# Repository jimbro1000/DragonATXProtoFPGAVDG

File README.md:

# Dragon ATX Prototype FPGA VDG

This repository contains the KiCad project files
to produce the VDG component board for my
ATX Prototype backplane.

This design requires the ATX backplane board in order 
to operate
See https://github.com/jimbro1000/DragonATXProto

## Notes

Revision 1 includes a more modern RGB fed modulator
design that removes a significant problem in the 
form of the old LM1889 modulator. The board also
provides the mounting points for the various mezzanine
boards that have been previously developed. If the
mezzanine option is to be used the rest of the card
should be left unpopulated

This design has been completed using KiCad 9. Earlier
versions of KiCad are not compatible

## Memory Map

| Address Range | Usage | Notes |
|:------------- |:----- |:----- |
| $0000 - $7FFF | Lower 32K RAM page | Can be remapped to the upper 32K using P1 under RAM/ROM memory map type |
| $8000 - $9FFF | Lower system ROM (R0) | The last 16 bytes are mapped to $FFF0 - $FFFF |
| $A000 - $BFFF | Upper system ROM (R1) | |
| $C000 - $FF00 | External ROM (R2) | |
| $C000 - $FF00 | Upper 32K RAM page | Under RAM only memory map type |
| $FF00 - $FFEF | SAM registers and Peripheral IO |
| $FF00 - $FF1F | PIA 0 & Serial port |
| $FF20 - $FF23 | PIA 1 |
| $FF24 - $FF27 | PIA 1b | video expansion slot |
| $FF28 - $FF2F | PIA 1c and 1d | audio expansion slot |
| $FF30 - $FF37 | PIA 1e and 1f | expansion slot 3 |
| $FF38 - $FF3F | PIA 1g and 1h | expansion slot 4 |
| $FF40 - $FF5F | PIA 2 | external |
| $FF60 - $FFBF | reserved |
| $FF90 | Set compatible mode | bit 7 (1) |
| $FF91 | Set task id | bits 0..2 (2)(3) |
| $FF92 | IRQ control bits | (4) |
| $FF93 | FIRQ control bits | (4) |
| $FF94 | MSB of timer |
| $FF95 | LSB of timer |
| $FFA0 | Select RAM paging register | Registers are selected for the current task only |
| $FFA1 | Upper byte of page register | |
| $FFA2 | Lower byte of page register | Writing to the lower byte commits changes to the selected register |
| $FFC0 - $FFDF | SAM |
| $FFE0 - $FFEF | reserved |
| $FFF0 - $FFFF | CPU vectors |

1. Compatibility mode forces the SAMx to behave as an original MC6883 SAM. Setting the bit to 1 turns compatibility on, clearing the bit enables the additional SAMx features. The other bits of the register are unused.

2. Tasks are identified by 3 bits - bits 0 to 2, 000 = task 0 (typically reserved for the operating system), 001 = task 1, 010 = task 2, 011 = task 3, 100 = task 4. (task ids 101 and 110 are reserved for VDG and library pages, 111 is associated with unallocated pages).

3. Bit 5 is used to specify the resolution of the timer, clearing the bit used a slow timer, setting the bit uses a fast timer.

4. The SAMx can generate interrupts according to the bit masks set for IRQ and FIRQ. The only bit defined at the moment is bit 5 and is triggered by the timer (counting down to 0). If the bit is cleared the SAMx will not generate an interrupt, if set the interrupt will be generated against the chosen interrupt line ($FF92 for IRQ, $FF93 for FIRQ). It is currently possible to specify an interrupt on both lines, in this situation FIRQ will be used.

5. In the RAM type memory map the paging for any of the registers can be set to bank of the ROM, in the RAM/ROM type memory map the R0 and R1 blocks need to behave differently. R0 at $8000 is mapped in 4 blocks to $00000 of the ROM by default, R1 is mapped to $A000 in 4 blocks at $02000. R2 is bound exclusively to the cartridge port ROM space at $C000, there is no mechanism to map this to a ROM bank. In RAM mode R2 can be mapped to a RAM or ROM bank but if a cartridge is fitted the paging is ignored and the cartridge ROM is used instead.

### Expanded Memory

| Address Range | Notes |
|:------------- |:----- |
| $000000 - $00FFFF | CPU addressable range |
| $000000 - $01FFFF | VDG addressable range |
| $000000 - $1FFFFF | Maximum onboard paged RAM |
| $000000 - $080000 | Maximum onboard paged ROM |

## Design

Unlike previous iterations that attempt to simply
replicate the original 6847 using CPLD hardware, this
design is aimed at a full upgrade and replacement for 
the 6847 and 6883. By combining the functionality of
the two chips are significant saving in complexity is
achieved. There is no longer a requirement to 
artificially synchronise the video against the CPU
clock cycle, this is inherent as the video clock is
tied directly to the cpu clock.

## SAM upgrades

The SAM replacement is based around the work done by
Ciaran Anscomb to upgrade the SAM to include RAM paging.
His design extended to 512KB which, while "adequate", 
is wasteful of the target FPGA device which includes
16MB of RAM. Of that 16MB only 2MB is directly accessed
as a single block. The 2MB is 16bit wide (technically 4MB)
but accessing both halves of the RAM adds extra complexity
to the read/write cycle, just using one half is definitely
simpler.

### SAM Registers ###

As a result of the SAM having full access to the databus the
internal registers can now be fully programmed with a single
write operation (or per bit if required). The registers are
expanded as necessary, for example the video base address is
extended to allow addressing of a much larger memory space,
and the introduction of new registers for process and memory
mapping.

#### Programmable Registers ####

| Register | Size | Usage |
| -------- | ---- | ----- |
| V | 3 bits | Video addressing mode - 4 bits in expanded mode - the extra bit is ignored unless the VDG compatibility mode is disabled |
| F | 7 bits | Video base addressing multiples of 512 bytes - 8 bits in expanded mode, after a vertical sync the VDG address counter bits 9 - 15 are loaded with the value held in F, the lower 8 bits are set to 0. In expanded mode bits 9-16 are loaded from F |
| P | 1 bit | RAM/ROM mode page register |
| R | 2 bits | CPU speed control |
| M | 2 bits | Used to define Memory size in original SAM, unused here |
| TY | 1 bit | Memory Map Type |

#### Internal Registers

| Register | Size | Usage |
| -------- | ---- | ----- |
| C | 7 bits | DRAM refresh counter - unused here |
| B | 16 bits | VDG address counter - 17 bits in expanded mode |
| N0..4x8 | 9 bits | Page Allocation Table (1) |
| NVx16 | 9 bits | Video Page Allocation Table (2) |
| Ox256 | 3 bits | Page Owner Table (3) |
| T | 3 bits | Current Task ID |
| VL | 1 bit | Video Page Lock (4) |

1. Each task has a set of 8 registers, each 9 bits in length. The MSB of each indicates
if the value is referencing RAM (0) or ROM (1). Each register defines an 8K address window
and what page of memory it is mapped to. Only one set of N registers is addressable at any
time dependent on the current task ID.

2. The Video "task" has its own set of page allocation registers and this extends to a 
total addressable space of 128K. The Video page registers are accessible to all tasks unless
the VL bit is set.

3. Each RAM page has a 4 bit identifier associated with, the value equates to one of
the task ids.

4. The Video Page lock restricts access to the video page registers to task id 0 (supervisor).
When set any attempts to modify the video page registers will be ignored.

### Memory Paging ###

The upgraded SAM provides MMU capabilities, both paging and process (page protection). With 256 8K pages in the address
space and each page can be allocated to RAM or ROM. Each process has its own page map.

Processes are either:

1. supervisor  
2. display
3. library (shared)
4. user process 1
5. user process 2
6. user process 3
7. user process 4

The shared process and display are used purely for identification of shared pages.

#### Display Process ####

The display process is used only for read operations by the VDG side of the clock cycle. The same pages can
be shared with the supervisor or a user process.

### Paging ###

Each process has its own map of 8K pages composed into the 64K memory space available directly to the CPU. The
only exception to this is the display process which has its own 128K memory space and is addressed only by the
VDG in this manner.

Each page has a permissions byte associated with it. The page is either unallocated (and can be acquired by any
process), or owned by one of the seven process ids. The display and library process pages are an exception and
can be shared between multiple processes.

The MMU maintains a page allocation table for all 256 available pages. Each process has its own address
translation map, only one map is presented to the CPU at a time, with the CPU address register translated
into the larger MMU address space.

### Rom Paging ###

Further to the available RAM pages the address map can reference pages from the ROM space. ROM pages are always
shared.

#### Rom Mapping At Cold Start ####

The MMU will always allocate the last page of the supervisor address space to the last ROM page to cover
the CPU vectors. The last ROM page should also include the bootstrap code to set the host into an operational
state.

At warm start the host will enter the supervisor process. Holding the host in reset for 2 seconds will
be treated as a cold start.

### Blitter ###

The blitter provides out-of-process memory copy in one of five operations:

1. Full page copy (8K copy from one page to another)
2. Continuous block copy (within process address space)
3. Shaped to continuous (within process address space)
4. Continuous to shaped (within process address space)
5. Shaped to shaped (within process address space)

All operations are defined by an origin, destination and byte length (maximum is 8K)

Shaped operations have two further parameters - width and gap. The width defines how many bytes in a row
are copied and the gap the number of bytes to skip to the next run of bytes

Copying can only be performed between pages allocated to the initiating process

Only a single blit operation can be performed at a time, all operations can be queued

The blit operates at the highest clock speed achievable by the RAM and SAM. Nominally this is 166MHz with a 3 cycle 
latency, the SAM operates at 28.6MHz and each byte copy takes 3 cycles. Effectively this means a copy rate of
8 bytes per CPU clock cycle (using interleaved access between CPU, VDG and Blitter) at regular 0.89MHz CPU
clock speeds. Running at a faster CPU speed would reduce the available slots for blit operations

The number of cycles for the blitter will be adjusted to suit the cpu and vdg clock speeds

A maximum copy speed can be achieved by halting the CPU and timing the blit start to the end of the vertical
display viewport. The slice allocation will reallocate CPU and VDG portions to the blitter - the result is
lightning fast block copy of ram. Page copy can run faster as it is guaranteed contiguous on both sides
meaning 64 bytes per copy cycle instead of 8 bytes. That is 128 CPU cycles (equivalent) to copy 8K at
page copy, 1024 cycles at shaped copy speeds but at the regular 0.895MHz that is still 0.001s to copy a
full 8K - in reality a shaped copy is likely to be much less than 8K in length. A regular high-res
screen is just 6K...

## VDG upgrades

The default operation mode for the VDG is full compatibility with the original MC6847. In practical
terms this means fixed display palettes (although these could still be modified through HDL source) and
standard resolutions.

With compatibility mode enabled all of the VDG control is as per the original device - external input for
Alpha/Semi, Alpha/Graphic, Graphic Mode, Inverse, Colour Set and Internal/External

With compatibility mode disabled the VDG expands control to a wide set of registers in the new
device (operated through the SAM for memory configuration and direct through a new memory
mapped device for mode). The default modes are still present but can be modified to suit, or
a new set of display modes can be used.

### VDG Registers

The upgraded VDG exists in mapped memory space, occupying 16 bytes. These form a set of registers
controlling how the video operates.

0. Video Mode Control - 8 bit flags for enabling features
1. Zero RAM Mode - left byte
2. Zero RAM Mode - right byte
3. Zero RAM Mode - palette
4. Palette - register select (0-47)
5. Palette - register data
6. Geometry - register select (0-7)
7. Geometry - register data
8. Sprite - sprite id select
9. Sprite - register select
10. Sprite - register data
11. Tile - tile id select
12. Tile - register select
13. Tile - register data
14. Counter - register select
15. Counter - register data

#### Video Mode Control

Bit 7 controls video display format, 1 = NTSC, 0 = PAL

Bit 6 controls the use of zero mode, 1 = enabled, 0 = disabled. Zero mode
is a zero ram mode that simply uses 2 static bytes of data per row, set 
using the zero ram mode registers.

Bit 5 enables tile mode. This is ignored in compatibility mode.

Bit 4 enables sprites. This is ignored in compatibility mode.

Bit 3 enables zero mode as an overlay. In this state the background colour is
always transparent.

Bit 2 enables the extended graphic modes. This is ignored in compatibility
mode.

Bit 1 is reserved for future use.

Bit 0 controls compatibility. 1 = extended options enabled, 0 = 6847
compatible.

#### Zero RAM Mode

Zero RAM mode operates without the need to load any data from RAM, combined
with a suitable ROM image this means the host system can display useful
diagnostic data without the need for working RAM. Zero RAM can also be 
enabled as an overlay over other display modes.

In Zero mode the display resolution is 16 pixels wide. The left hand side
of the display is register 1, the right hand side is register 2.

Register 1 is the first 8 bits of each row, the same data is displayed
vertically for the entire viewport unless changed mid-frame. Register is the final
8 bits of each row with the same behaviour vertically.

Register 3 controls the colour of the display, the first 4 bits define the
foreground, the last 8 bits define the background. In overlay mode the background
is always transparent.

The colours are each 4 bit TTL RGB with half bright. In the case of black the half
bright equivalent is a darker shade of grey than white with half bright.

#### Palette Control

The VDG supports 24 different programmable entries in its palette. Each one is 12 bits
of RGB and require two palette registers to access each one. Even palette registers represent 
the upper 4 bits (red) of each entry, odd palette entries represent the lower 8 bits (green and
blue) of each entry.

The first palette register (4) selects which palette entry is being referenced. With two
registers per entry the value must be multiplied by two for each entry.

The second palette register (5) defines the data of the selected palette entry.

#### Geometry Control

In the extended modes the display geometry can be modified, significantly increasing the
flexibility of thos modes.

VDG Register 6 selects which of the geometry registers is active. VDG Register 7 accesses 
the value of each.

0. Upper 2 bits of the viewport X position on screen.
1. Lower 8 bits of the viewport X position.
2. Upper 1 bit of the viewport y position.
3. Lower 8 bits of the viewport y position.
4. Viewport width (in bytes, 0-63).
5. Viewport height (in rows, 0-255).
6. Upper 1 bit of the display height (in rows).
7. Lower 8 bits of the display height.

More geometry registers may be added as new features are introduced.

#### Sprite Control

Sprites are relatively complex objects in this system. Each sprite Id can be a graphic
definition, or it can be a path object that sets how the sprite moves

VDG Register 8 selects which sprite Id is active, VDG Register 9 selects the address of the object
data. Each sprite object can be up to 255 bytes long.

VDG Register 10 access the data of the object.

#### Tile Control

Tiles are handled in much the same way as sprites for the purposes of defining them.

VDG Register 11 selects which tile Id is referenced (0-255). VDG Register 12 sets
the address within the selected tile object. VDG Register 13 accesses the tile data at
the given address.

#### Counters

A small number of counters can be defined to automatically trigger actions based on
the row or column of the current display frame.

VDG Register 14 selects which counter register is active. VDG Register 15
accesses the data for the selected counter.

### Display Layers

The display presented to the screen is composed of a series of layers.

Top most are sprites, these always have a transparency and appear over all
other graphical detail.

The next layer down is the "regular" bitmap graphic mode. If no other layers
are enabled the "0" colour will be visible, otherwise it will be transparent.

Below the bitmap mode lies the zero mode. As with the bitmap mode if tile mode
is not enabled the background colour is visible, otherwise it will be transparent.

The lowest layer is the tile mode. This has no transparency and every position
on the display must have a tile.

The composition of layers in this way offers the maximum flexibility from the
capabilities of the enhanced VDG.

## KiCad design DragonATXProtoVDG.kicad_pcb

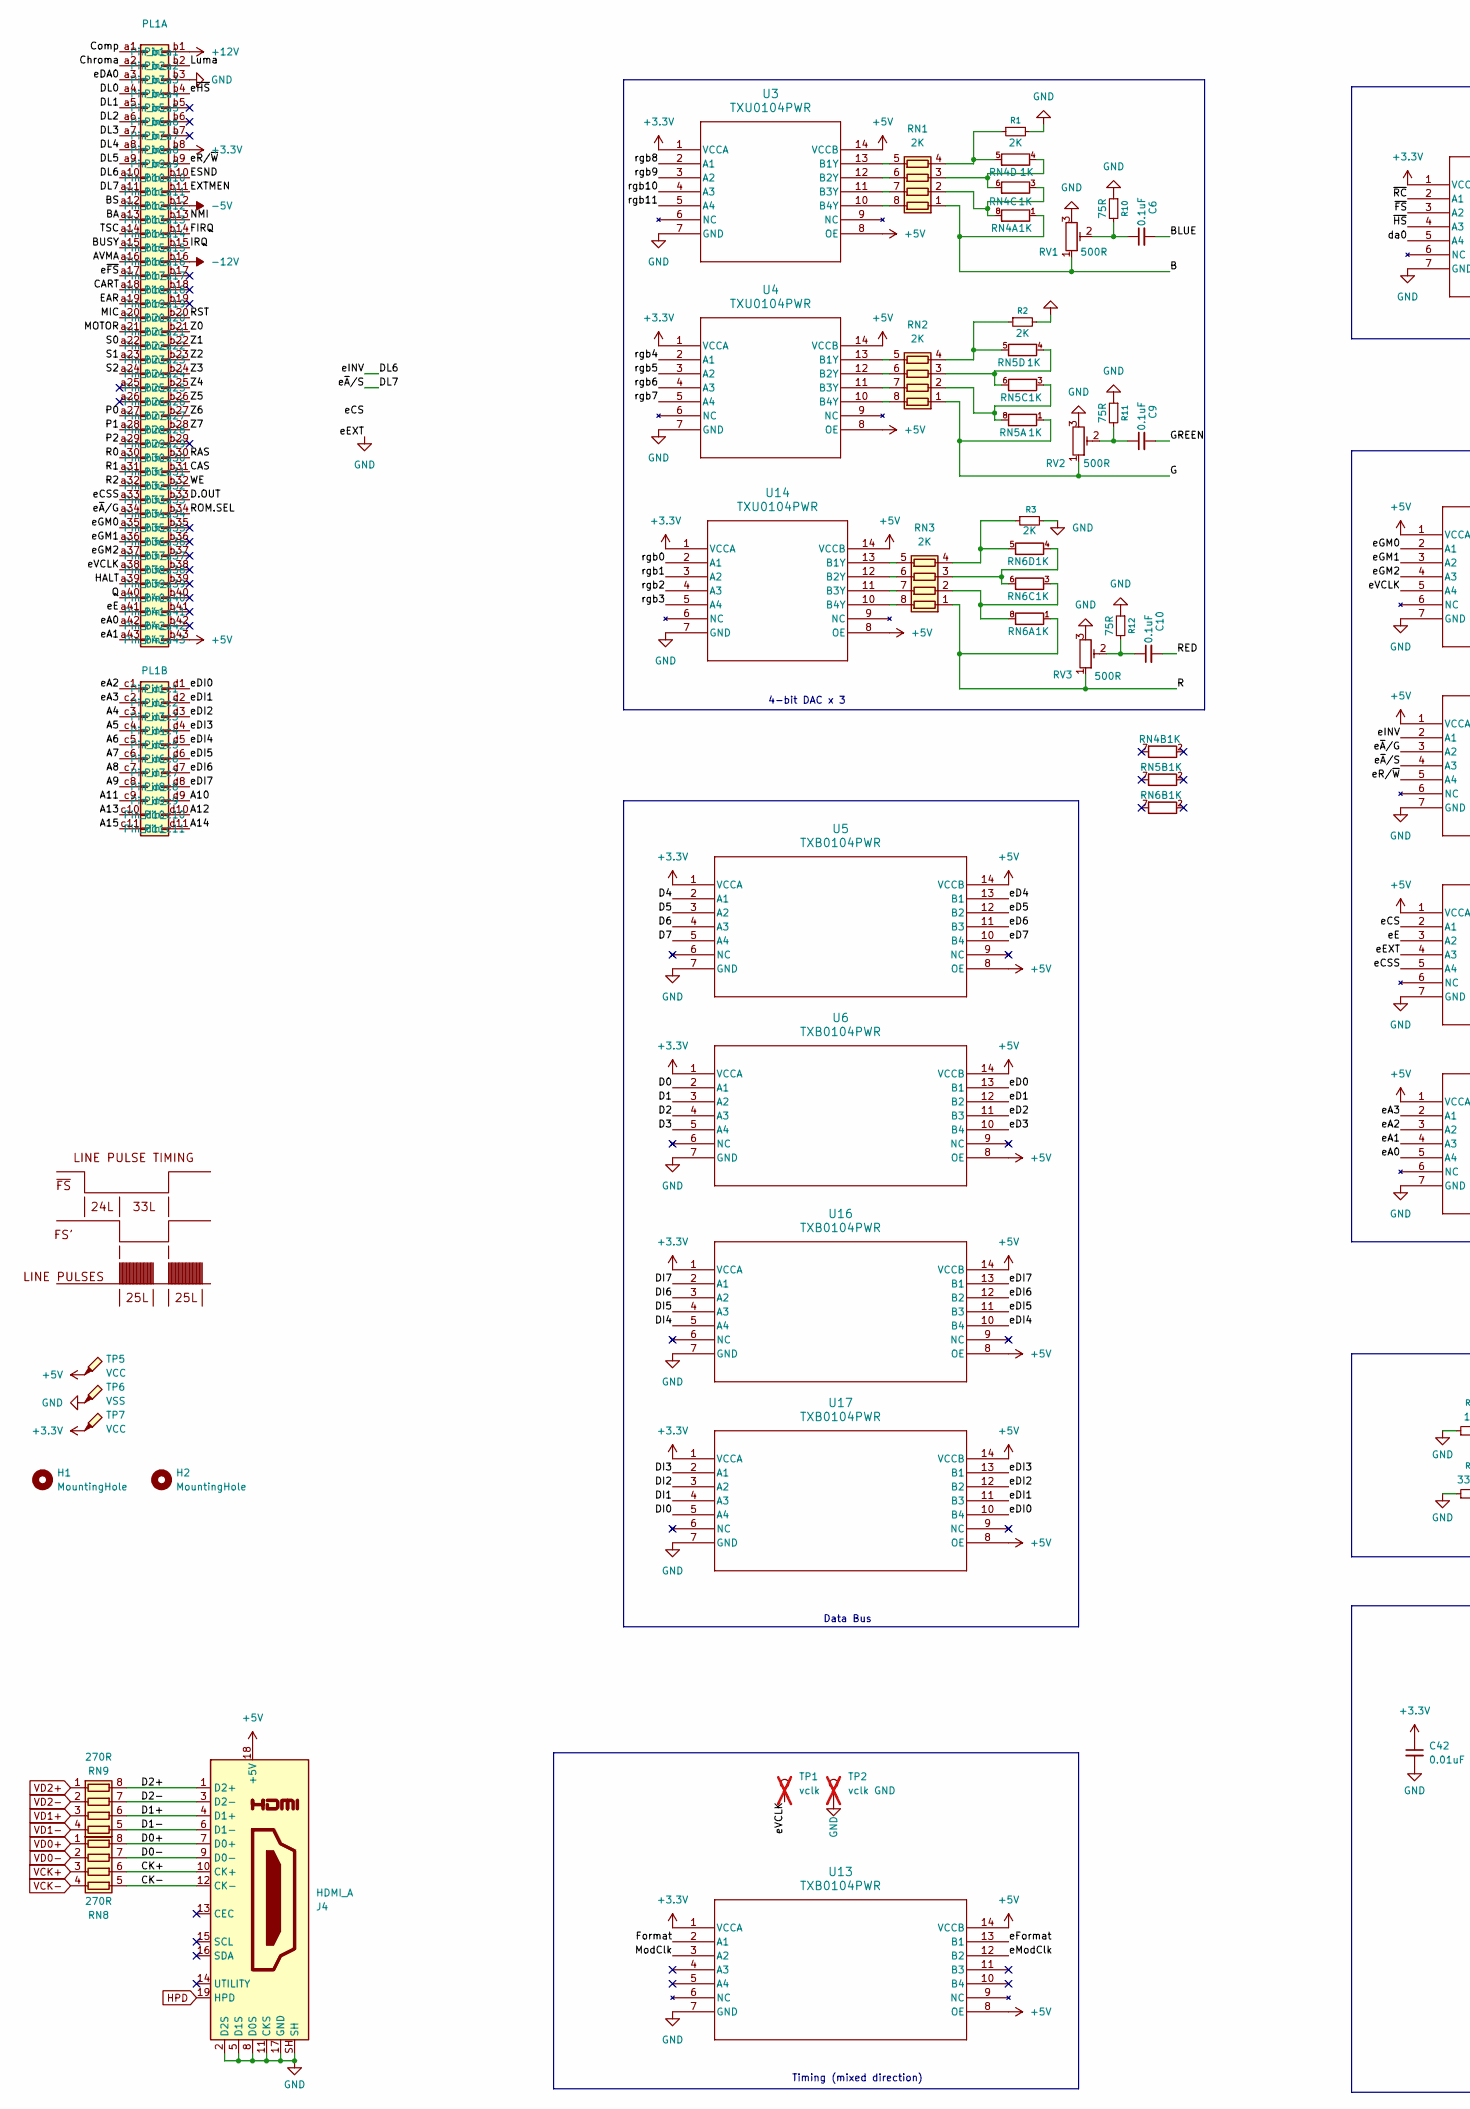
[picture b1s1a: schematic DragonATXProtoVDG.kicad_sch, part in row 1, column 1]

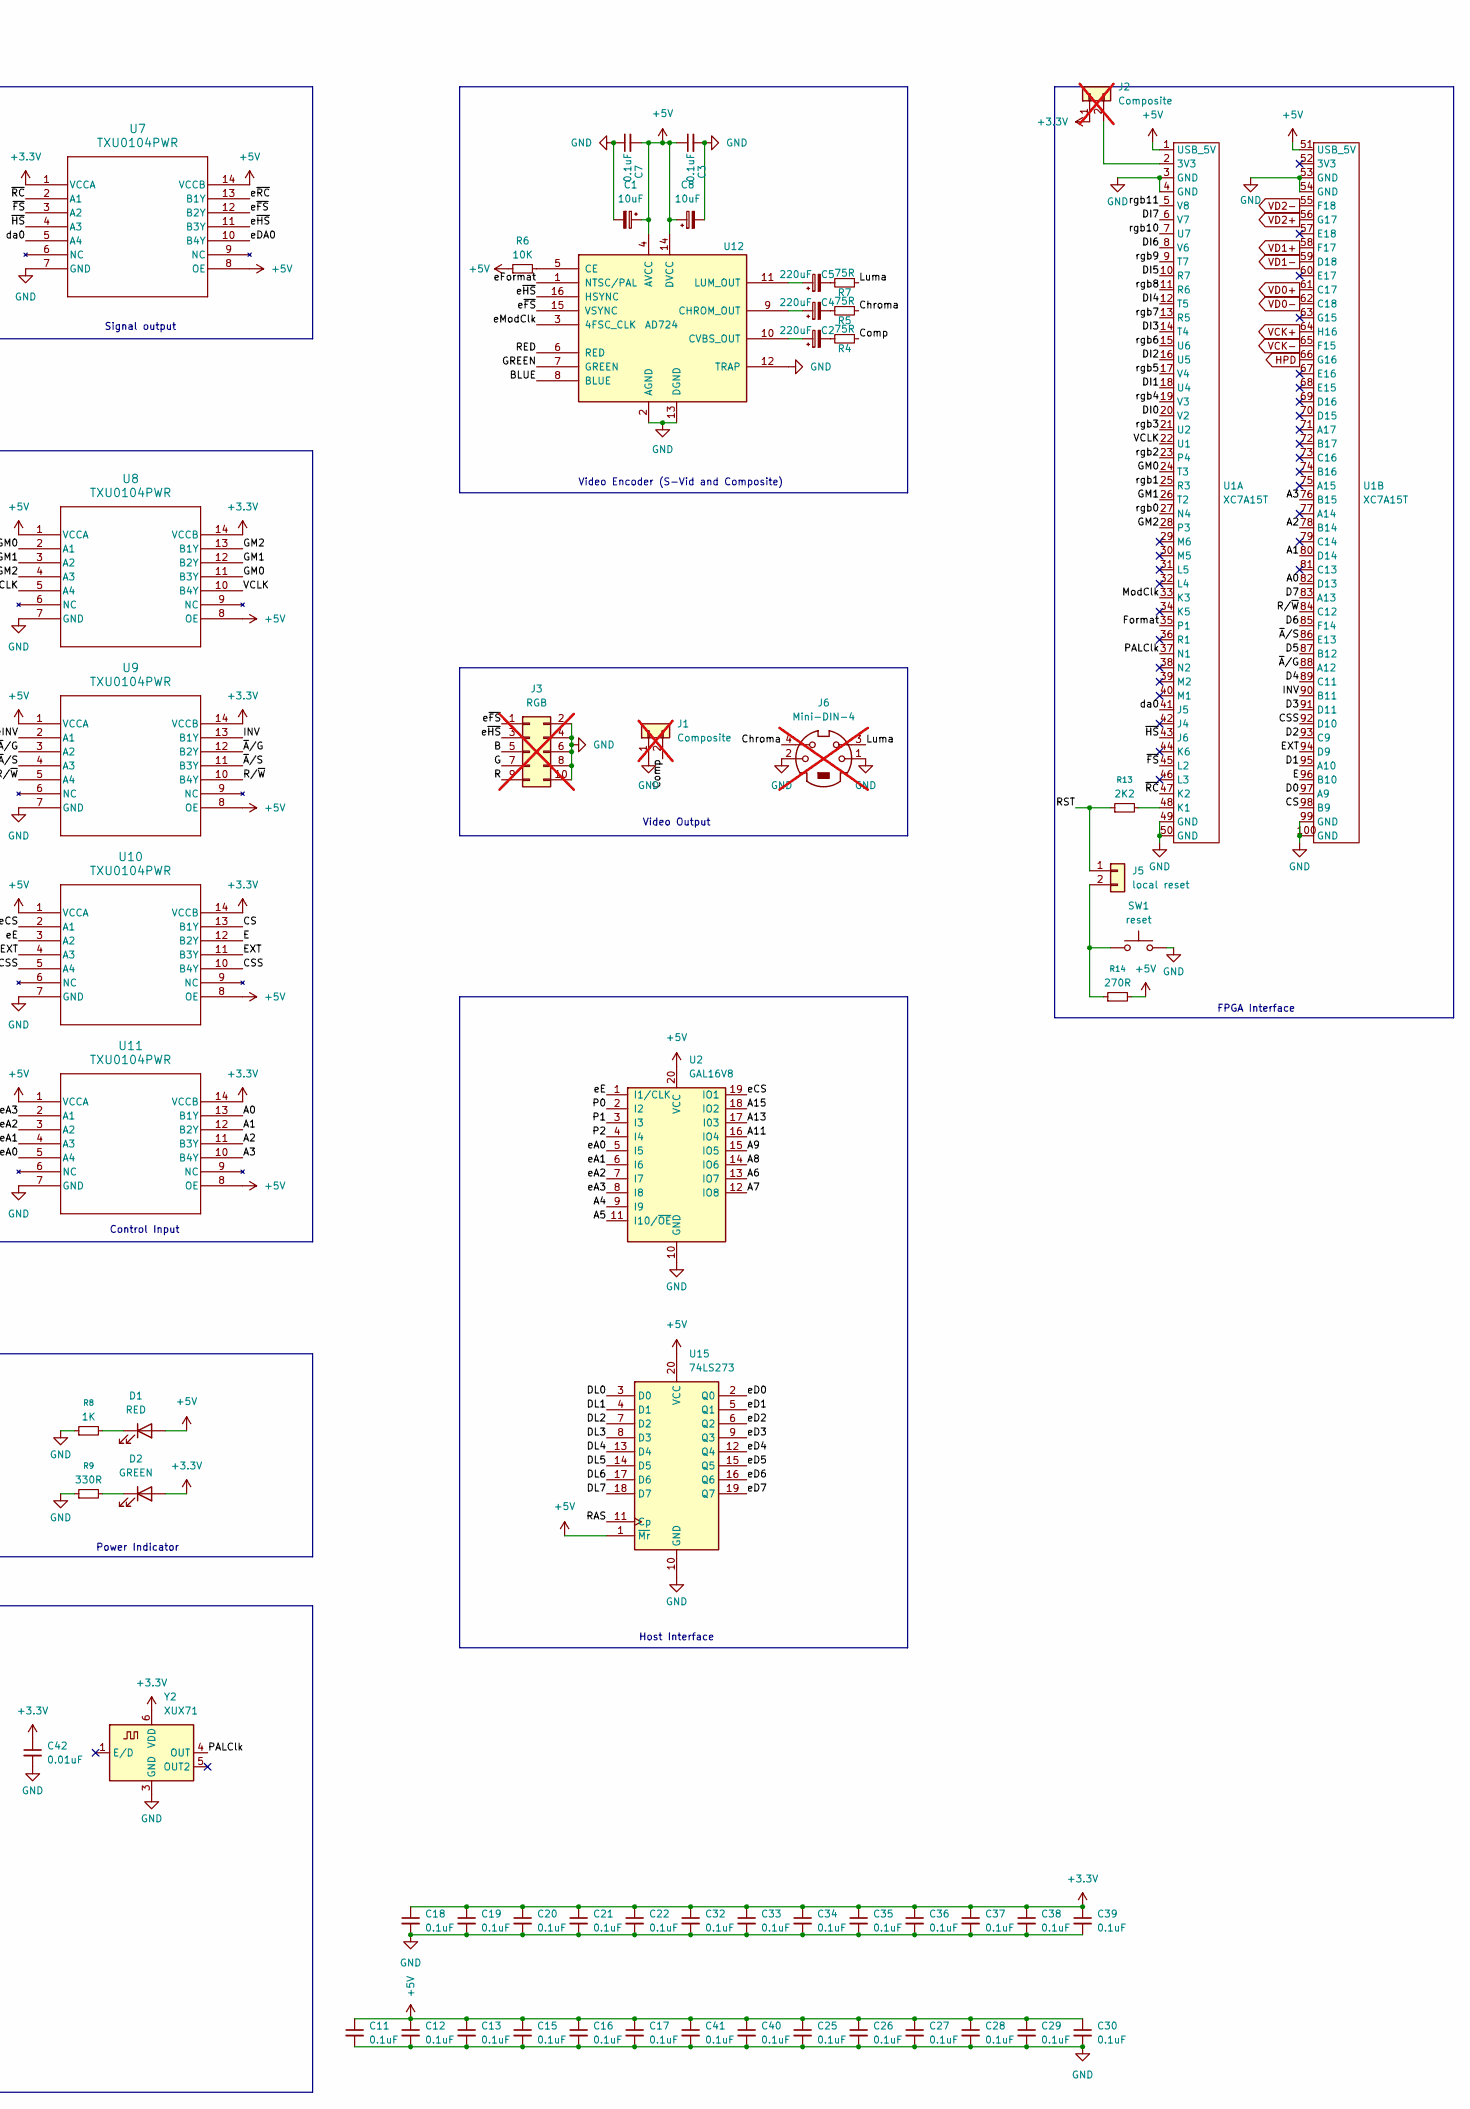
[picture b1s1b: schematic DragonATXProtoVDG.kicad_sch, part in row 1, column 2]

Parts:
C1, C8: 10uF; CP_EIA-3216-18_Kemet-A; DigiKey 399-3683-1-ND
C2, C4, C5: 220uF; CP_EIA-3528-21_Kemet-B; DigiKey 399-T490B227M006ATE300CT-ND
C3, C6, C7, C9, C10, C11, C12, C13, C15, C16, C17, C18, C19, C20, C21, C22, C25, C26, C27, C28, C29, C30, C32, C33, C34, C35, C36, C37, C38, C39, C40, C41: 0.1uF; C_0603_1608Metric; LCSC C14663
C42: 0.01uF; C_0603_1608Metric; LCSC C57112
D1: RED; D_0805_2012Metric; LCSC C84256
D2: GREEN; D_0805_2012Metric; LCSC C2297
H1, H2: MountingHole; MountingHole_3.2mm_M3
J1: Composite; CUI_RCJ-041; not fitted
J2: Composite; PinHeader_1x02_P2.54mm_Vertical; not fitted
J3: RGB; IDC-Header_2x05_P2.54mm_Latch_Horizontal; not fitted
J4: HDMI_A; HDMI_A_Amphenol_10029449-x01xLF_Horizontal
J5: local reset; SolderJumper-2_P1.3mm_Open_Pad1.0x1.5mm
J6: Mini-DIN-4; MINI-DIN-4; not fitted
PL1: Card_Edge
R1, R2, R3: 2K; R_0603_1608Metric; LCSC C22975
R4, R5, R7: 75R; R_0603_1608Metric; DigiKey RMCF0603FT75R0CT-ND
R6: 10K; R_0603_1608Metric; DigiKey RMCF0603JT10K0CT-ND
R8: 1K; R_0603_1608Metric; DigiKey RMCF0603FT1K00CT-ND
R9: 330R; R_0603_1608Metric; DigiKey RMCF0603JT330RCT-ND
R10, R11, R12: 75R; R_0603_1608Metric; LCSC C4275
R13: 2K2; R_0603_1608Metric; DigiKey RMCF0603FT1K00CT-ND
R14: 270R; R_0603_1608Metric; DigiKey RMCF0603FT1K00CT-ND
RN1, RN2, RN3: 2K; R_Array_Convex_4x1206; DigiKey 13-YC324-FK-072KLCT-ND
RN4, RN5, RN6: 1K; R_Array_Convex_4x1206; DigiKey 13-YC324-FK-071KLCT-ND
RN8, RN9: 270R; R_Array_Convex_4x1206; DigiKey 13-YC324-FK-072KLCT-ND
RV1, RV2, RV3: 500R; Potentiometer_Bourns_3314J_Vertical; DigiKey 3314J-501ECT-ND
SW1: reset; SW_Tactile_SPST_NO_Straight_CK_PTS636Sx25SMTRLFS
TP1: vclk; TestPoint_Pad_D1.5mm; not fitted
TP2: vclk GND; TestPoint_Pad_D1.5mm; not fitted
TP5, TP7: VCC; TestPoint_Loop_D3.80mm_Drill2.0mm
TP6: VSS; TestPoint_Loop_D3.80mm_Drill2.0mm
U1: XC7A15T; QMTECH_XC7A15T
U2: GAL16V8; PLCC-20_THT-Socket
U3, U4, U7, U8, U9, U10, U11, U14: TXU0104PWR; TSSOP_0104PWR; DigiKey 296-TXU0104PWRCT-ND
U5, U6, U13, U16, U17: TXB0104PWR; TSSOP_0104PWR; DigiKey 296-21929-1-ND
U12: AD724; SOIC-16W_7.5x10.3mm_P1.27mm
U15: 74LS273; TSSOP-20_4.4x6.5mm_P0.65mm; DigiKey 1727-7301-1-ND
Y2: XUX71; Oscillator_SMD_IDT_JU6-6_7.0x5.0mm_P2.54mm; Mouser 972-XLH735004433619X
Z1: LINE_PULSE_DIAGRAM

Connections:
+3.3V: C18.1, C19.1, C20.1, C21.1, C22.1, C32.1, C33.1, C34.1, C35.1, C36.1, C37.1, C38.1, C39.1, C42.1, D2.2 (A), J2.1, PL1.b8, TP7.1, U3.1 (VCCA), U4.1 (VCCA), U5.1 (VCCA), U6.1 (VCCA), U7.1 (VCCA), U8.14 (VCCB), U9.14 (VCCB), U10.14 (VCCB), U11.14 (VCCB), U13.1 (VCCA), U14.1 (VCCA), U16.1 (VCCA), U17.1 (VCCA), Y2.6 (VDD)
+5V: C1.1, C3.1, C7.2, C8.1, C11.1, C12.1, C13.1, C15.1, C16.1, C17.1, C25.1, C26.1, C27.1, C28.1, C29.1, C30.1, C40.1, C41.1, D1.2 (A), J4.18 (+5V), PL1.b43, R6.1, R14.2, TP5.1, U1.1 (USB_5V), U1.51 (USB_5V), U2.20 (VCC), U3.8 (OE), U3.14 (VCCB), U4.8 (OE), U4.14 (VCCB), U5.8 (OE), U5.14 (VCCB), U6.8 (OE), U6.14 (VCCB), U7.8 (OE), U7.14 (VCCB), U8.1 (VCCA), U8.8 (OE), U9.1 (VCCA), U9.8 (OE), U10.1 (VCCA), U10.8 (OE), U11.1 (VCCA), U11.8 (OE), U12.4 (AVCC), U12.14 (DVCC), U13.8 (OE), U13.14 (VCCB), U14.8 (OE), U14.14 (VCCB), U15.1 (~Mr), U15.20 (VCC), U16.8 (OE), U16.14 (VCCB), U17.8 (OE), U17.14 (VCCB)
+12V: PL1.b1
-5V: PL1.b12
-12V: PL1.b16
/A0: U1.82 (D13), U11.13 (B1Y)
/A1: U1.80 (D14), U11.12 (B2Y)
/A2: U1.78 (B14), U11.11 (B3Y)
/A3: U1.76 (B15), U11.10 (B4Y)
/A4: PL1.c3, U2.9 (I9)
/A5: PL1.c4, U2.11 (I10/~OE)
/A6: PL1.c5, U2.13 (IO7)
/A7: PL1.c6, U2.12 (IO8)
/A8: PL1.c7, U2.14 (IO6)
/A9: PL1.c8, U2.15 (IO5)
/A10: PL1.d9
/A11: PL1.c9, U2.16 (IO4)
/A12: PL1.d10
/A13: PL1.c10, U2.17 (I03)
/A14: PL1.d11
/A15: PL1.c11, U2.18 (IO2)
/AVMA: PL1.a16
/B: J3.5, RN1.1 (R1.1), RN4.1 (R1.1), RV1.1
/BA: PL1.a13
/BLUE: C6.2, U12.8 (BLUE)
/BS: PL1.a12
/BUSY: PL1.a15
/CART: PL1.a18
/CAS: PL1.b31
/CK+: J4.10 (CK+), RN8.6 (R3.2)
/CK-: J4.12 (CK-), RN8.5 (R4.2)
/CS: U1.98 (B9), U10.13 (B1Y)
/CSS: U1.92 (D10), U10.10 (B4Y)
/Chroma: J6.4, PL1.a2, R5.1
/Comp: J1.2, PL1.a1, R4.1
/D0: U1.97 (A9), U6.2 (A1)
/D0+: J4.7 (D0+), RN8.8 (R1.2)
/D0-: J4.9 (D0-), RN8.7 (R2.2)
/D1: U1.95 (A10), U6.3 (A2)
/D1+: J4.4 (D1+), RN9.6 (R3.2)
/D1-: J4.6 (D1-), RN9.5 (R4.2)
/D2: U1.93 (C9), U6.4 (A3)
/D2+: J4.1 (D2+), RN9.8 (R1.2)
/D2-: J4.3 (D2-), RN9.7 (R2.2)
/D3: U1.91 (D11), U6.5 (A4)
/D4: U1.89 (C11), U5.2 (A1)
/D5: U1.87 (B12), U5.3 (A2)
/D6: U1.85 (F14), U5.4 (A3)
/D7: U1.83 (A13), U5.5 (A4)
/D.OUT: PL1.b33
/DI0: U1.20 (V2), U17.5 (A4)
/DI1: U1.18 (U4), U17.4 (A3)
/DI2: U1.16 (U5), U17.3 (A2)
/DI3: U1.14 (T4), U17.2 (A1)
/DI4: U1.12 (T5), U16.5 (A4)
/DI5: U1.10 (R7), U16.4 (A3)
/DI6: U1.8 (V6), U16.3 (A2)
/DI7: U1.6 (V7), U16.2 (A1)
/DL0: PL1.a4, U15.3 (D0)
/DL1: PL1.a5, U15.4 (D1)
/DL2: PL1.a6, U15.7 (D2)
/DL3: PL1.a7, U15.8 (D3)
/DL4: PL1.a8, U15.13 (D4)
/DL5: PL1.a9, U15.14 (D5)
/DL6: PL1.a10, U9.2 (A1), U15.17 (D6)
/DL7: PL1.a11, U9.4 (A3), U15.18 (D7)
/E: U1.96 (B10), U10.12 (B2Y)
/EAR: PL1.a19
/ESND: PL1.b10
/EXT: U1.94 (D9), U10.11 (B3Y)
/EXTMEN: PL1.b11
/FIRQ: PL1.b14
/Format: U1.35 (P1), U13.2 (A1)
/G: J3.7, RN2.1 (R1.1), RN5.1 (R1.1), RV2.1
/GM0: U1.24 (T3), U8.11 (B3Y)
/GM1: U1.26 (T2), U8.12 (B2Y)
/GM2: U1.28 (P3), U8.13 (B1Y)
/GREEN: C9.2, U12.7 (GREEN)
/HALT: PL1.a39
/INV: U1.90 (B11), U9.13 (B1Y)
/IRQ: PL1.b15
/Luma: J6.3, PL1.b2, R7.1
/MIC: PL1.a20
/MOTOR: PL1.a21
/ModClk: U1.33 (K3), U13.3 (A2)
/NMI: PL1.b13
/P0: PL1.a27, U2.2 (I2)
/P1: PL1.a28, U2.3 (I3)
/P2: PL1.a29, U2.4 (I4)
/PALClk: U1.37 (N1), Y2.4 (OUT)
/Q: PL1.a40
/R: J3.9, RN3.1 (R1.1), RN6.1 (R1.1), RV3.1
/R0: PL1.a30
/R1: PL1.a31
/R2: PL1.a32
/RAS: PL1.b30, U15.11 (Cp)
/RED: C10.2, U12.6 (RED)
/ROM.SEL: PL1.b34
/RST: J5.1, PL1.b20, R13.1
/R/~W: U1.84 (C12), U9.10 (B4Y)
/S0: PL1.a22
/S1: PL1.a23
/S2: PL1.a24
/TSC: PL1.a14
/VCLK: U1.22 (U1), U8.10 (B4Y)
/WE: PL1.b32
/Z0: PL1.b21
/Z1: PL1.b22
/Z2: PL1.b23
/Z3: PL1.b24
/Z4: PL1.b25
/Z5: PL1.b26
/Z6: PL1.b27
/Z7: PL1.b28
/da0: U1.41 (J5), U7.5 (A4)
/eA0: PL1.a42, U2.5 (I5), U11.5 (A4)
/eA1: PL1.a43, U2.6 (I6), U11.4 (A3)
/eA2: PL1.c1, U2.7 (I7), U11.3 (A2)
/eA3: PL1.c2, U2.8 (I8), U11.2 (A1)
/eCS: U2.19 (IO1), U10.2 (A1)
/eCSS: PL1.a33, U10.5 (A4)
/eD0: U6.13 (B1), U15.2 (Q0)
/eD1: U6.12 (B2), U15.5 (Q1)
/eD2: U6.11 (B3), U15.6 (Q2)
/eD3: U6.10 (B4), U15.9 (Q3)
/eD4: U5.13 (B1), U15.12 (Q4)
/eD5: U5.12 (B2), U15.15 (Q5)
/eD6: U5.11 (B3), U15.16 (Q6)
/eD7: U5.10 (B4), U15.19 (Q7)
/eDA0: PL1.a3, U7.10 (B4Y)
/eDI0: PL1.d1, U17.10 (B4)
/eDI1: PL1.d2, U17.11 (B3)
/eDI2: PL1.d3, U17.12 (B2)
/eDI3: PL1.d4, U17.13 (B1)
/eDI4: PL1.d5, U16.10 (B4)
/eDI5: PL1.d6, U16.11 (B3)
/eDI6: PL1.d7, U16.12 (B2)
/eDI7: PL1.d8, U16.13 (B1)
/eE: PL1.a41, U2.1 (I1/CLK), U10.3 (A2)
/eFormat: U12.1 (NTSC/PAL), U13.13 (B1)
/eGM0: PL1.a35, U8.2 (A1)
/eGM1: PL1.a36, U8.3 (A2)
/eGM2: PL1.a37, U8.4 (A3)
/eModClk: U12.3 (4FSC_CLK), U13.12 (B2)
/eR/~W: PL1.b9, U9.5 (A4)
/eVCLK: PL1.a38, TP1.1, U8.5 (A4)
/e~A/G: PL1.a34, U9.3 (A2)
/e~FS: J3.1, PL1.a17, U7.12 (B2Y), U12.15 (VSYNC)
/e~HS: J3.3, PL1.b4, U7.11 (B3Y), U12.16 (HSYNC)
/e~RC: U7.13 (B1Y)
/rgb0: U1.27 (N4), U14.2 (A1)
/rgb1: U1.25 (R3), U14.3 (A2)
/rgb2: U1.23 (P4), U14.4 (A3)
/rgb3: U1.21 (U2), U14.5 (A4)
/rgb4: U1.19 (V3), U4.2 (A1)
/rgb5: U1.17 (V4), U4.3 (A2)
/rgb6: U1.15 (U6), U4.4 (A3)
/rgb7: U1.13 (R5), U4.5 (A4)
/rgb8: U1.11 (R6), U3.2 (A1)
/rgb9: U1.9 (T7), U3.3 (A2)
/rgb10: U1.7 (U7), U3.4 (A3)
/rgb11: U1.5 (V8), U3.5 (A4)
/~A/G: U1.88 (A12), U9.12 (B2Y)
/~A/S: U1.86 (E13), U9.11 (B3Y)
/~FS: U1.45 (L2), U7.3 (A2)
/~HS: U1.43 (J6), U7.4 (A3)
/~RC: U1.47 (K2), U7.2 (A1)
GND: C1.2, C3.2, C7.1, C8.2, C11.2, C12.2, C13.2, C15.2, C16.2, C17.2, C18.2, C19.2, C20.2, C21.2, C22.2, C25.2, C26.2, C27.2, C28.2, C29.2, C30.2, C32.2, C33.2, C34.2, C35.2, C36.2, C37.2, C38.2, C39.2, C40.2, C41.2, C42.2, J1.1, J3.2, J3.4, J3.6, J3.8, J3.10, J4.2 (D2S), J4.5 (D1S), J4.8 (D0S), J4.11 (CKS), J4.17 (GND), J4.SH, J6.1, J6.2, PL1.b3, R1.2, R2.2, R3.2, R8.1, R9.1, R10.1, R11.1, R12.1, RV1.3, RV2.3, RV3.3, SW1.2, TP2.1, TP6.1, U1.3 (GND), U1.4 (GND), U1.49 (GND), U1.50 (GND), U1.53 (GND), U1.54 (GND), U1.99 (GND), U1.100 (GND), U2.10 (GND), U3.7 (GND), U4.7 (GND), U5.7 (GND), U6.7 (GND), U7.7 (GND), U8.7 (GND), U9.7 (GND), U10.4 (A3), U10.7 (GND), U11.7 (GND), U12.2 (AGND), U12.12 (TRAP), U12.13 (DGND), U13.7 (GND), U14.7 (GND), U15.10 (GND), U16.7 (GND), U17.7 (GND), Y2.3 (GND)
HPD: J4.19 (HPD), U1.66 (G16)
unnamed: C2.2, R4.2
unnamed: C4.2, R5.2
unnamed: C5.2, R7.2
unnamed: C6.1, R10.2, RV1.2
unnamed: C9.1, R11.2, RV2.2
unnamed: C10.1, R12.2, RV3.2
unnamed: D1.1 (K), R8.2
unnamed: D2.1 (K), R9.2
unnamed: J2.2, U1.2 (3V3)
unnamed: J5.2, R14.1, SW1.1
unnamed: RN1.8 (R1.2), U3.10 (B4Y)
unnamed: RN1.2 (R2.1), RN4.3 (R3.1), RN4.8 (R1.2)
unnamed: RN1.7 (R2.2), U3.11 (B3Y)
unnamed: RN1.3 (R3.1), RN4.4 (R4.1), RN4.6 (R3.2)
unnamed: RN1.6 (R3.2), U3.12 (B2Y)
unnamed: R1.1, RN1.4 (R4.1), RN4.5 (R4.2)
unnamed: RN1.5 (R4.2), U3.13 (B1Y)
unnamed: RN2.8 (R1.2), U4.10 (B4Y)
unnamed: RN2.2 (R2.1), RN5.3 (R3.1), RN5.8 (R1.2)
unnamed: RN2.7 (R2.2), U4.11 (B3Y)
unnamed: RN2.3 (R3.1), RN5.4 (R4.1), RN5.6 (R3.2)
unnamed: RN2.6 (R3.2), U4.12 (B2Y)
unnamed: R2.1, RN2.4 (R4.1), RN5.5 (R4.2)
unnamed: RN2.5 (R4.2), U4.13 (B1Y)
unnamed: RN3.8 (R1.2), U14.10 (B4Y)
unnamed: RN3.2 (R2.1), RN6.3 (R3.1), RN6.8 (R1.2)
unnamed: RN3.7 (R2.2), U14.11 (B3Y)
unnamed: RN3.3 (R3.1), RN6.4 (R4.1), RN6.6 (R3.2)
unnamed: RN3.6 (R3.2), U14.12 (B2Y)
unnamed: R3.1, RN3.4 (R4.1), RN6.5 (R4.2)
unnamed: RN3.5 (R4.2), U14.13 (B1Y)
unnamed: R13.2, U1.48 (K1)
unnamed: R6.2, U12.5 (CE)
unnamed: C4.1, U12.9 (CHROM_OUT)
unnamed: C2.1, U12.10 (CVBS_OUT)
unnamed: C5.1, U12.11 (LUM_OUT)
VCK+: RN8.3 (R3.1), U1.64 (H16)
VCK-: RN8.4 (R4.1), U1.65 (F15)
VD0+: RN8.1 (R1.1), U1.61 (C17)
VD0-: RN8.2 (R2.1), U1.62 (C18)
VD1+: RN9.3 (R3.1), U1.58 (F17)
VD1-: RN9.4 (R4.1), U1.59 (D18)
VD2+: RN9.1 (R1.1), U1.56 (G17)
VD2-: RN9.2 (R2.1), U1.55 (F18)

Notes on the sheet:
Signal output
Data Bus
4-bit DAC x 3
Timing (mixed direction)
Host Interface
Power Indicator
FPGA Interface
Video Output
Video Encoder (S-Vid and Composite)
Control Input

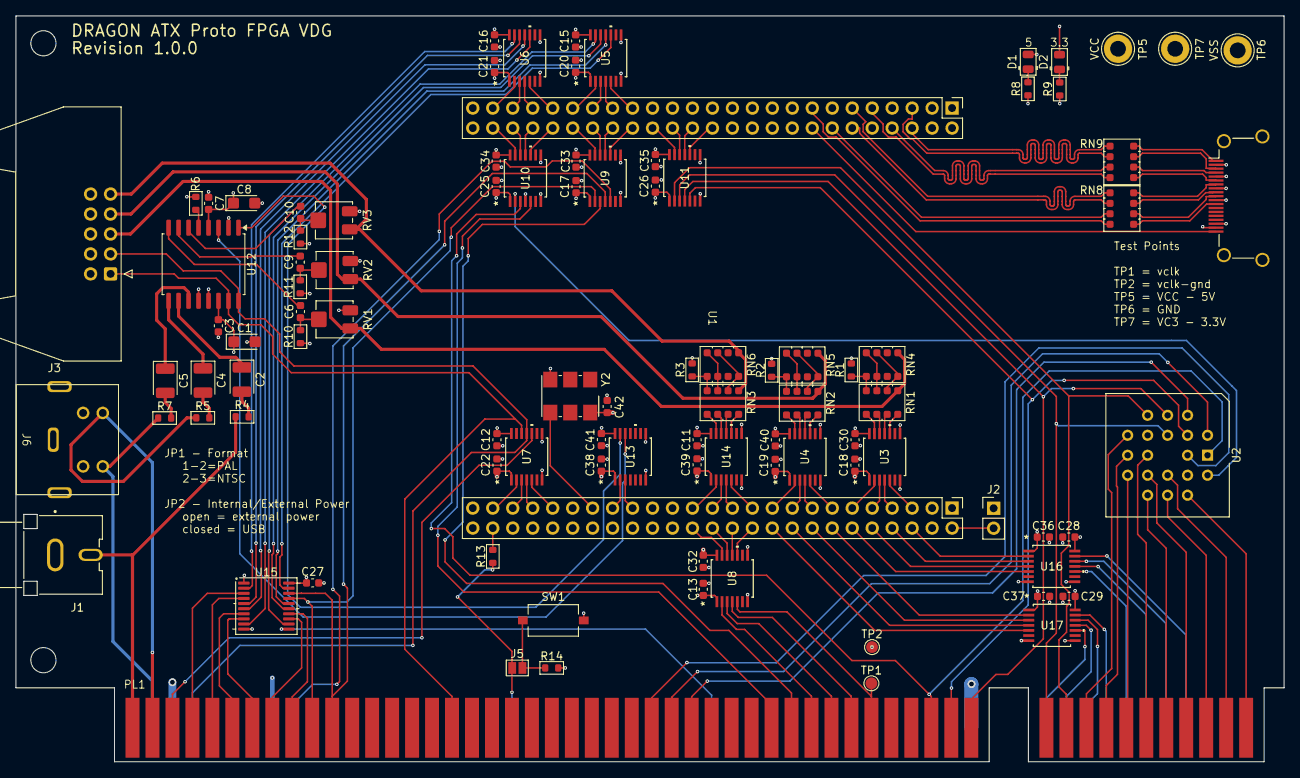
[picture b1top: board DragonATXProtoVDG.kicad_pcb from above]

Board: 4 copper layers, 161.3 x 94.9 mm, 98 parts (0 on the bottom side), 172 nets.

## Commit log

2026-02-10 rewrite readme
